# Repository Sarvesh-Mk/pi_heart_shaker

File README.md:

# Pi Heart-Sound Shaker HAT

**A Raspberry Pi HAT that plays heart sounds through a bass shaker, so you can *feel* them through a stethoscope or a manikin.**

The Pi plays audio over I²S → an Adafruit MAX98357A class-D amp → a Dayton Audio TT25-8 tactile transducer ("puck" shaker). Put the shaker under a manikin's chest or a pad, put a stethoscope on it, and you get realistic normal/abnormal heart sounds for clinical skills practice (e.g. OSCE stations). One button skips to the next track; another safely shuts the Pi down.

| Front | Back |
|---|---|
|  |  |

---

## At a glance

| | |
|---|---|
| **Form factor** | Standard Pi HAT outline, 65 × 56.5 mm, 4 × M2.5 mounting holes |
| **Layers** | 2-layer PCB |
| **Fits** | Any Pi with a 40-pin header (Zero 2 W, 3, 4, 5) |
| **Audio path** | Pi I²S → MAX98357A breakout (3 W, mono) → TT25-8 shaker (8 Ω) |
| **Controls** | `NEXT` button (GPIO17), `SHUTDOWN/WAKE` button (GPIO3), optional off-board button header |
| **Power** | 5 V from the Pi's 40-pin header (USB power bank works fine) |
| **Tool** | KiCad 8.0 |
| **Status** | Rev 1 — DRC 0 violations, ERC 0 errors ([reports](docs/reports/)) |

---

## Repository layout

```
pi_heart_shaker/
├── pi_heart_shaker.kicad_pro     KiCad project — open this
├── pi_heart_shaker.kicad_sch     Schematic
├── pi_heart_shaker.kicad_pcb     PCB layout
├── fp-lib-table                  Points KiCad at the project footprint library
├── pi_heart_shaker.pretty/       Project footprints (TT25-8 shaker 3D placeholder)
├── 3d/                           3D models (MAX98357A breakout, TT25-8 shaker) for renders
├── software/
│   ├── heart_player.py           Player: loops a track, NEXT button skips
│   ├── heart-player.service      systemd unit (starts the player at boot)
│   ├── install.sh                One-shot installer for Raspberry Pi OS
│   └── sounds/                   Put your .wav heart-sound recordings here
├── fab/
│   ├── gerbers/                  Gerbers + drill files, ready to upload to a fab
│   ├── bom.csv                   Short BOM (on-PCB parts)
│   └── bom_full.csv              Full build list incl. off-board parts
└── docs/
    ├── schematic.pdf             Schematic export (read without KiCad)
    ├── renders/                  3D renders
    └── reports/                  DRC / ERC reports
```

---

## How it works

```
 Raspberry Pi                       HAT                          off-board
┌─────────────┐   I²S (BCLK/LRC/DIN)   ┌──────────────────┐  speaker +/-  ┌──────────────┐
│ GPIO18/19/21├────────────────────────►│ MAX98357A (J2)   ├──────────────►│ TT25-8 puck  │
│        5 V  ├────────────────────────►│ Vin              │               │ bass shaker  │
│      GPIO17 │◄── SW1 NEXT / J3 ext.   └──────────────────┘               └──────────────┘
│       GPIO3 │◄── SW2 SHUTDOWN / WAKE
└─────────────┘
```

### Pin map

| Signal | Pi header pin | Pi GPIO | Goes to |
|---|---|---|---|
| `I2S_BCLK` | 12 | GPIO18 | J2-2 (BCLK) |
| `I2S_LRCLK` | 35 | GPIO19 | J2-1 (LRC) |
| `I2S_DIN` | 40 | GPIO21 | J2-3 (DIN) |
| `BTN_NEXT` | 11 | GPIO17 | SW1, J3-1 (to GND, use internal pull-up) |
| `BTN_SHUTDOWN` | 5 | GPIO3 | SW2 (to GND) |
| `+5V` | 2, 4 | — | J2-7 (Vin) |
| `GND` | 6, 9, 14, 20, 25, 30, 34, 39 | — | J2-6, buttons, JP1 |
| `AMP_GAIN` | — | — | J2-4 ↔ JP1 |

J2-5 (`SD`, amp shutdown) is left unconnected, so the amp is always on and outputs a (L+R)/2 mono mix.

### Amp gain (JP1)

| JP1 | MAX98357A GAIN pin | Gain |
|---|---|---|
| Open (default) | floating | 9 dB |
| Bridged with solder | GND | 12 dB |

---

## Bill of materials

- Adafruit I²S 3W Class D Amplifier Breakout — MAX98357A (Adafruit #3006)
- Dayton Audio TT25-8 tactile transducer (8 Ω)
- Raspberry Pi with 40-pin header (Zero 2 W needs a header soldered on)
- microSD card with Raspberry Pi OS
- 5 V USB power bank
- 4 × M2.5 standoffs + screws
- 2-conductor speaker wire

---

## Building one

1. **Order the PCB.** Zip the contents of [`fab/gerbers/`](fab/gerbers/) and upload to any PCB fab (JLCPCB, PCBWay, OSH Park…). Defaults are fine: 2 layers, 1.6 mm, any colour.
2. **Solder the HAT.**
   - J1 (2×20 socket) goes on the **bottom** side.
   - J2, J3, SW1, SW2 on the top.
   - Optionally bridge JP1 for 12 dB gain.
3. **Prepare the amp.** Solder the pin header that ships with the MAX98357A breakout so it plugs into J2 (pin order on the silkscreen: LRC, BCLK, DIN, GAIN, SD, GND, VIN).
4. **Wire the shaker** to the breakout's `+`/`-` screw terminal.
5. **Mount** on the Pi with M2.5 standoffs.

---

## Pi software

The [`software/`](software/) folder holds a small Python player that starts at boot:

- It **loops** the current heart-sound recording through the shaker.
- **NEXT** (SW1 or the J3 off-board button) skips to the next `.wav` file, in filename order, and goes back to the first after the last.
- **SHUTDOWN/WAKE** (SW2) safely powers the Pi down, and pressing it again wakes it. This needs no code: the `gpio-shutdown` overlay handles it.
- The script finds the MAX98357A sound card automatically.

### Install

On a Pi running Raspberry Pi OS (Bookworm or newer):

```bash
git clone <this repo> pi_heart_shaker
cd pi_heart_shaker/software
cp ~/my-heart-sounds/*.wav sounds/      # 01_normal.wav, 02_aortic_stenosis.wav, ...
sudo bash install.sh
sudo reboot
```

`install.sh`:

1. Installs `python3-gpiozero` and `alsa-utils`.
2. Copies the player to `/opt/heart-shaker/` and your recordings to `/opt/heart-shaker/sounds/`.
3. Adds these lines to `config.txt`, after saving a backup copy as `config.txt.bak-heart-shaker`:
   ```ini
   dtparam=audio=off
   dtoverlay=max98357a
   dtoverlay=gpio-shutdown
   ```
4. Installs and enables the `heart-player` systemd service.

### Use and troubleshooting

```bash
journalctl -u heart-player -f            # watch which track is playing
sudo systemctl restart heart-player      # after changing settings
aplay -l                                 # the MAX98357A should appear as a sound card
speaker-test -c 2 -t sine -f 60          # low test tone (stop the service first)
```

To add or change recordings later, copy them into `/opt/heart-shaker/sounds/`. The player picks them up the next time a track starts. See [`software/sounds/README.md`](software/sounds/README.md) for tips on preparing files.

To run it by hand without the service: `python3 heart_player.py --sounds ./sounds` (options: `--device`, `--next-pin`).

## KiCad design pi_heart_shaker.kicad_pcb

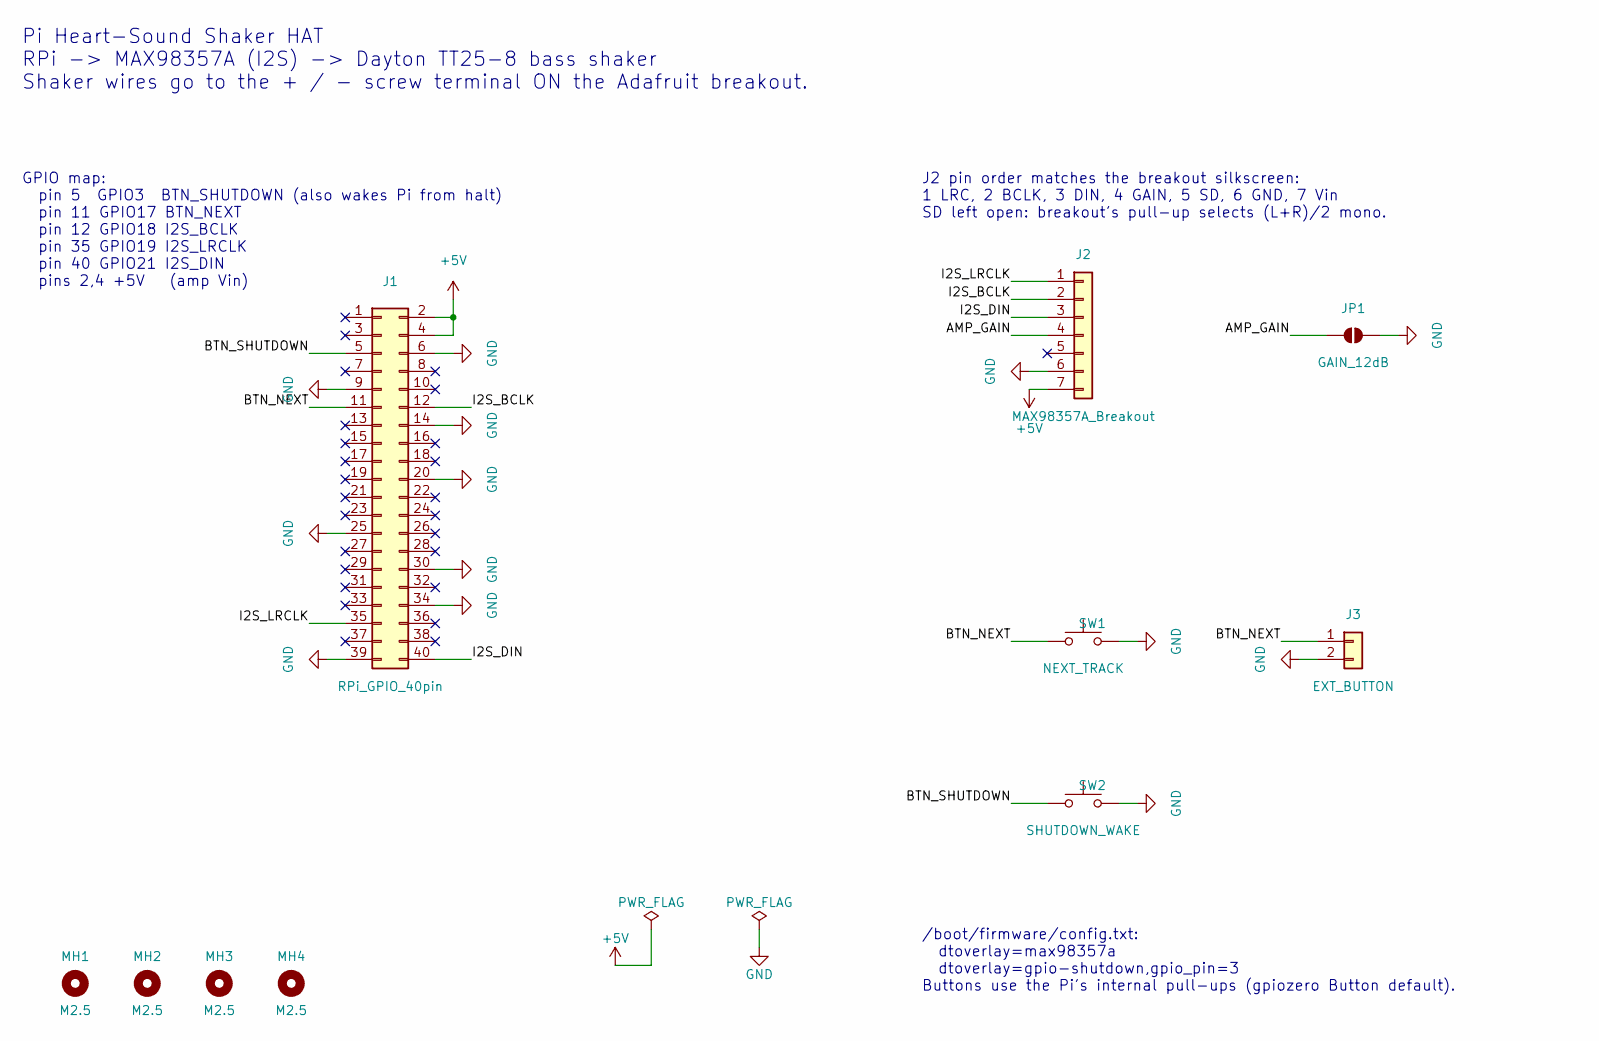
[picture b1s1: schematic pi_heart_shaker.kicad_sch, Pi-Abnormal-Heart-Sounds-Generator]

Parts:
J1: RPi_GPIO_40pin; PinSocket_2x20_P2.54mm_Vertical
J2: MAX98357A_Breakout; PinSocket_1x07_P2.54mm_Vertical
J3: EXT_BUTTON; PinHeader_1x02_P2.54mm_Vertical
JP1: GAIN_12dB; SolderJumper-2_P1.3mm_Open_RoundedPad1.0x1.5mm
MH1, MH2, MH3, MH4: M2.5; MountingHole_2.7mm_M2.5
SW1: NEXT_TRACK; SW_PUSH_6mm
SW2: SHUTDOWN_WAKE; SW_PUSH_6mm

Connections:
+5V: J1.2, J1.4, J2.7
/AMP_GAIN: J2.4, JP1.1 (A)
/BTN_NEXT: J1.11, J3.1, SW1.1
/BTN_SHUTDOWN: J1.5, SW2.1
/I2S_BCLK: J1.12, J2.2
/I2S_DIN: J1.40, J2.3
/I2S_LRCLK: J1.35, J2.1
GND: J1.6, J1.9, J1.14, J1.20, J1.25, J1.30, J1.34, J1.39, J2.6, J3.2, JP1.2 (B), SW1.2, SW2.2

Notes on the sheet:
Pi Heart-Sound Shaker HAT RPi -> MAX98357A (I2S) -> Dayton TT25-8 bass shaker Shaker wires go to the + / - screw terminal ON the Adafruit breakout.
/boot/firmware/config.txt: dtoverlay=max98357a dtoverlay=gpio-shutdown,gpio_pin=3 Buttons use the Pi's internal pull-ups (gpiozero Button default).
J2 pin order matches the breakout silkscreen: 1 LRC, 2 BCLK, 3 DIN, 4 GAIN, 5 SD, 6 GND, 7 Vin SD left open: breakout's pull-up selects (L+R)/2 mono.
GPIO map: pin 5 GPIO3 BTN_SHUTDOWN (also wakes Pi from halt) pin 11 GPIO17 BTN_NEXT pin 12 GPIO18 I2S_BCLK pin 35 GPIO19 I2S_LRCLK pin 40 GPIO21 I2S_DIN pins 2,4 +5V (amp Vin)

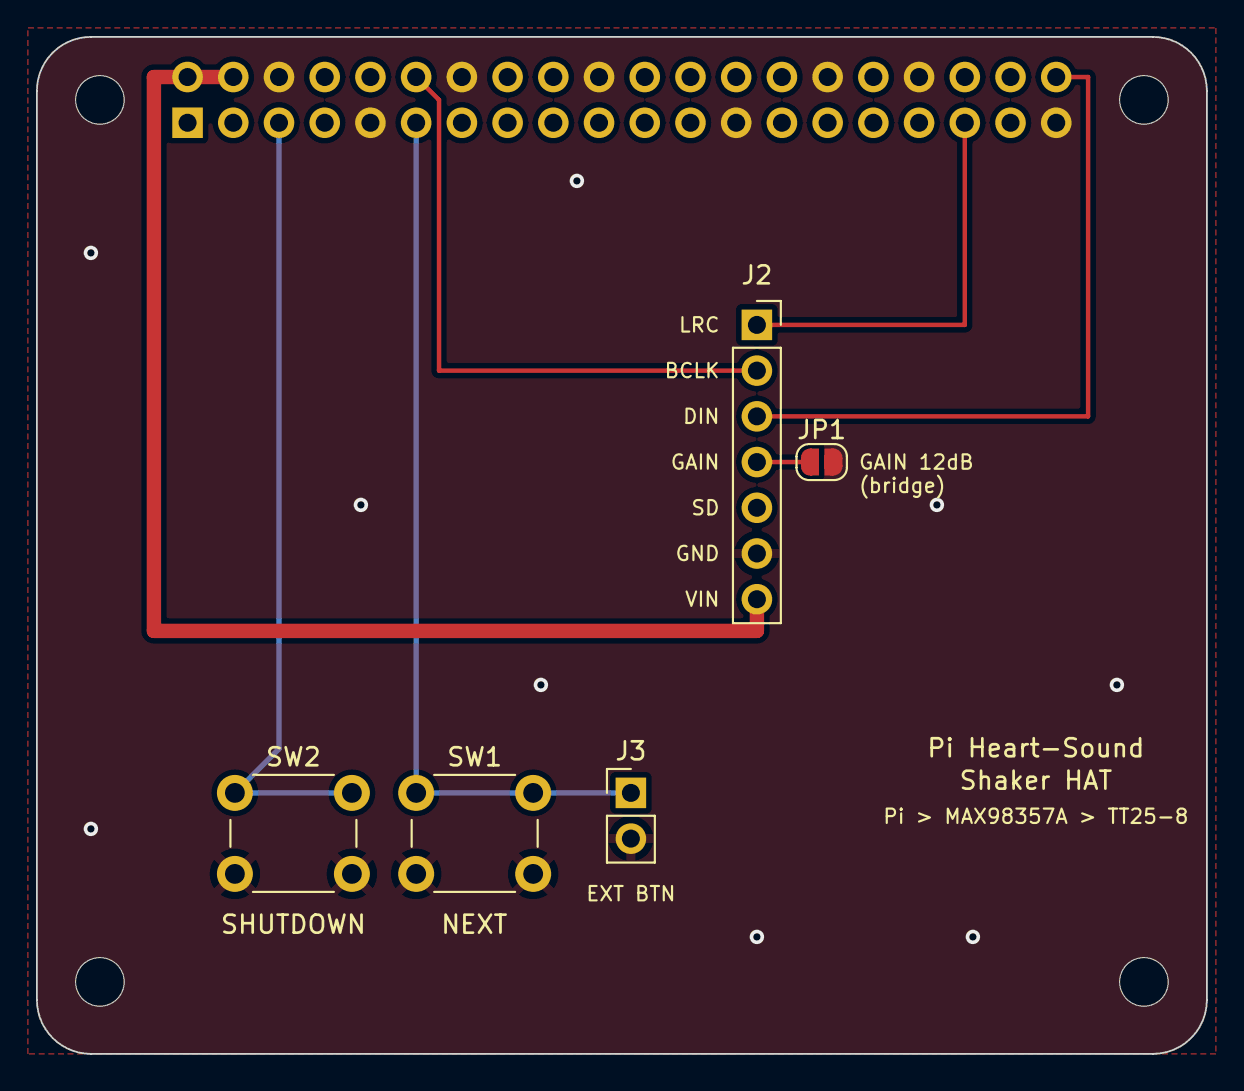
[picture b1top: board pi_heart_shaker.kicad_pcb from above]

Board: 2 copper layers, 65.0 x 56.5 mm, 11 parts (1 on the bottom side), 8 nets.

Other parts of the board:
SHK1: Dayton TT25-8 (off-board); Dayton_TT25-8_PUCK_3D

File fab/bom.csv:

"Refs","Value","Footprint","Qty","Description"
"J1","RPi_GPIO_40pin","Connector_PinSocket_2.54mm:PinSocket_2x20_P2.54mm_Vertical","1","Raspberry Pi 40-pin GPIO header (2x20 female socket on the underside of this HAT)"
"J2","MAX98357A_Breakout","Connector_PinSocket_2.54mm:PinSocket_1x07_P2.54mm_Vertical","1","Socket for Adafruit MAX98357A I2S 3W class-D amp breakout (#3006)"
"J3","EXT_BUTTON","Connector_PinHeader_2.54mm:PinHeader_1x02_P2.54mm_Vertical","1","Optional off-board button wired in parallel with SW1"
"SW1","NEXT_TRACK","Button_Switch_THT:SW_PUSH_6mm","1","Examiner button: next heart-sound track (GPIO17, internal pull-up)"
"SW2","SHUTDOWN_WAKE","Button_Switch_THT:SW_PUSH_6mm","1","Safe shutdown / wake (GPIO3, dtoverlay=gpio-shutdown)"
